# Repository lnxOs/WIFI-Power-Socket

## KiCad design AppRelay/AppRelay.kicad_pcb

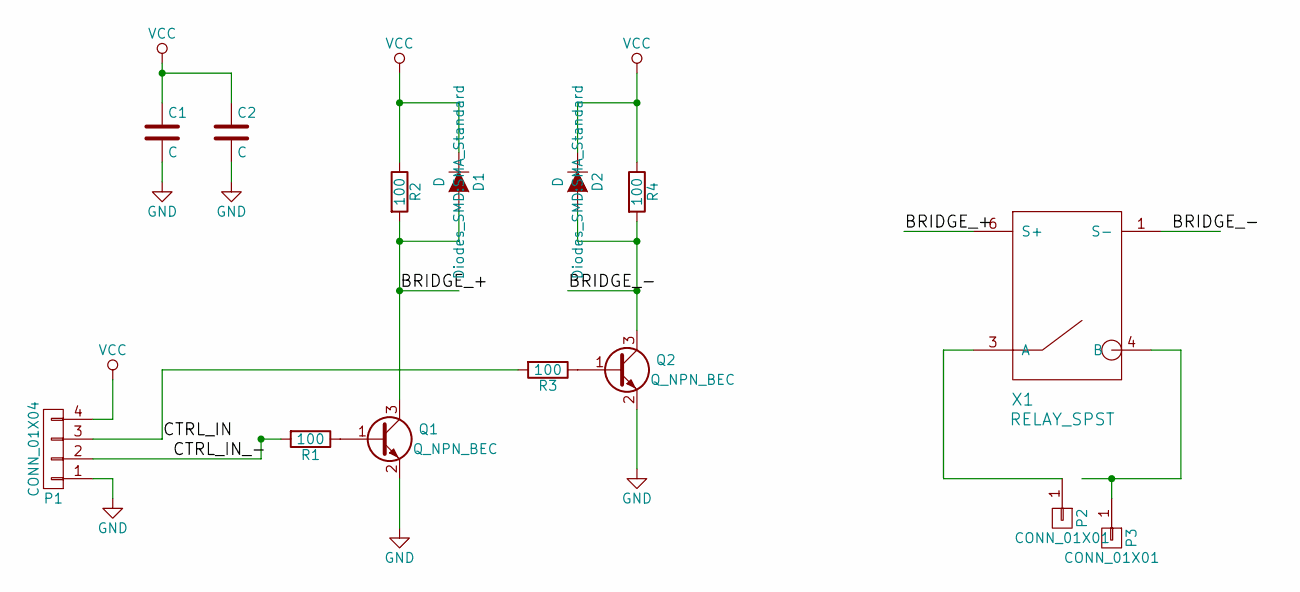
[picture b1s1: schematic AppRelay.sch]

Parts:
C1, C2: C; C_0805
D1, D2: D; SMA_Standard
P1: CONN_01X04; Pin_Header_Straight_1x04
P2, P3: CONN_01X01; Pin_Header_Straight_1x01
Q1, Q2: Q_NPN_BEC; SOT-23
R1, R2, R3, R4: 100; R_0805
X1: RELAY_SPST; G6BU-1114P-US-DC12

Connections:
/BRIDGE_+: D1.2 (A), Q1.3 (C), R2.2, X1.6 (S+)
/BRIDGE_-: D2.2 (A), Q2.3 (C), R4.2, X1.1 (S-)
/CTRL_IN: P1.3, R3.2
/CTRL_IN_-: P1.2, R1.2
GND: C1.2, C2.2, P1.1, Q1.2 (E), Q2.2 (E)
unnamed: P2.1, X1.3 (A)
unnamed: P3.1, X1.4 (B)
unnamed: Q1.1 (B), R1.1
unnamed: Q2.1 (B), R3.1
VCC: C1.1, C2.1, D1.1 (K), D2.1 (K), P1.4, R2.1, R4.1

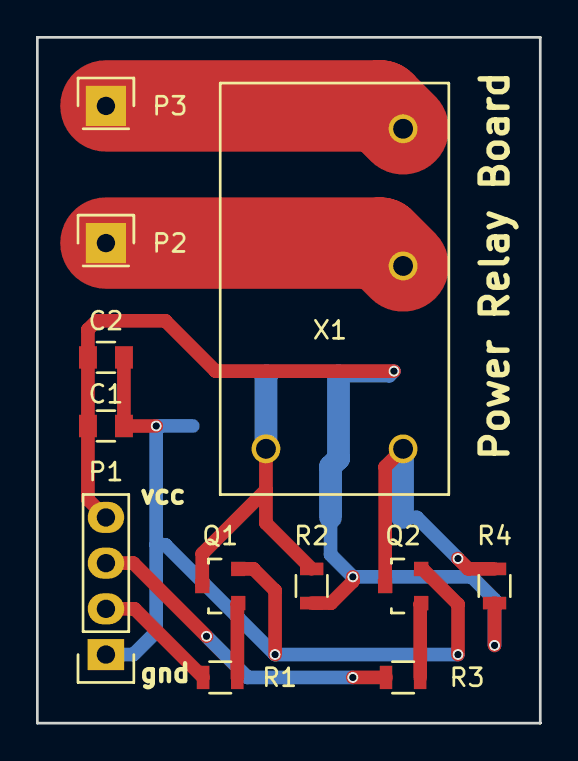
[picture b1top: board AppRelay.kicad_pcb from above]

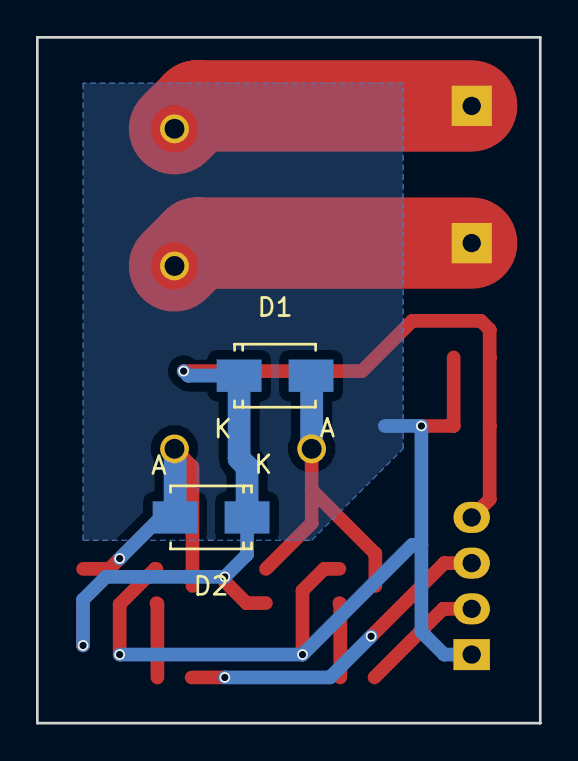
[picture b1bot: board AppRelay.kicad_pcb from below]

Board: 2 copper layers, 27.9 x 38.1 mm, 14 parts (2 on the bottom side), 10 nets.

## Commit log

2016-10-09 Initial commit. Contains readme template and APPRelay Kicad project.
2016-10-09 Added suggested NPN driver part numbers.
2016-10-13 Added file structure for WIFI-GPIO development.
2016-10-15 Fixed makefile configuration and tested flash. Ready for programming.
